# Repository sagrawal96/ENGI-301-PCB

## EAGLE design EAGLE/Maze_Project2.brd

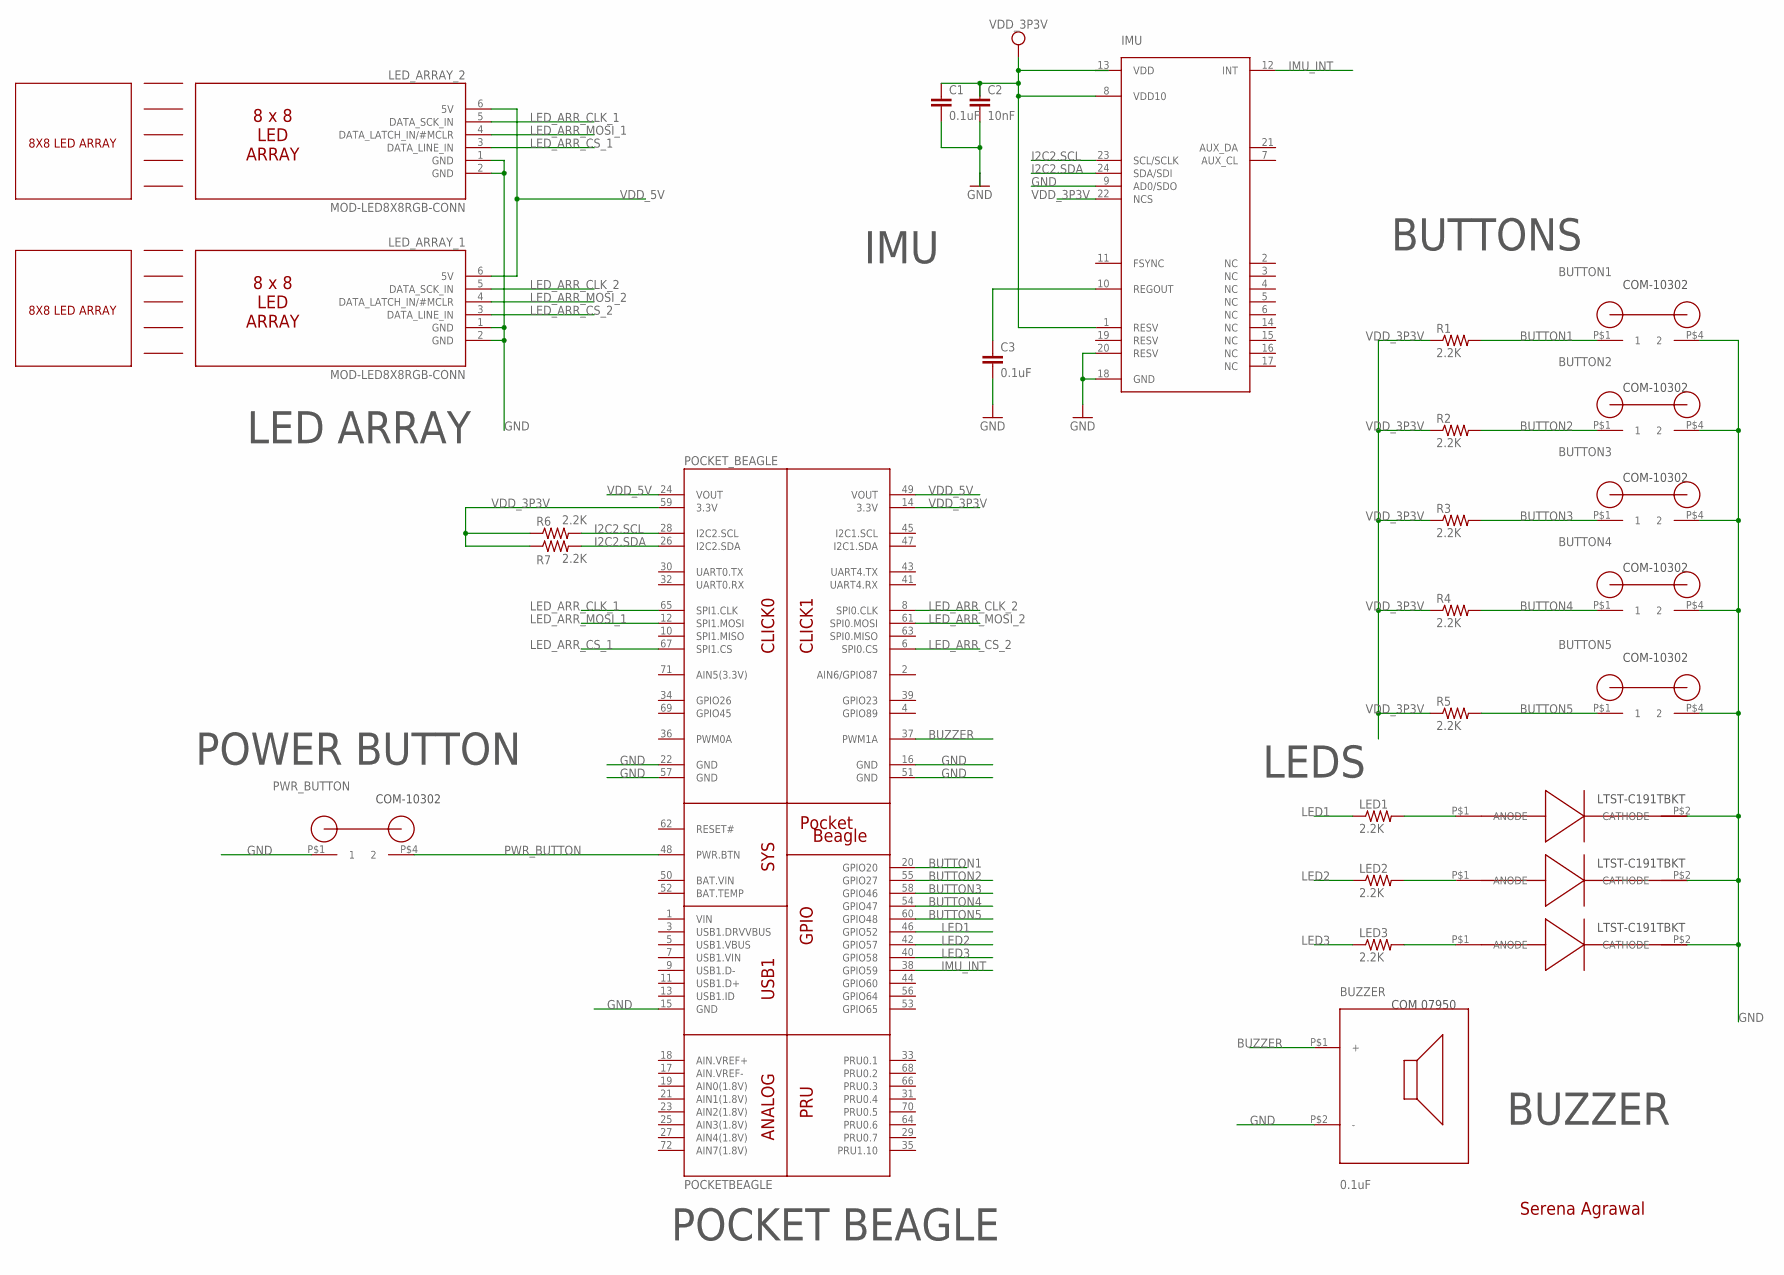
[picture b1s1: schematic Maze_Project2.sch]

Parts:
BUTTON1, BUTTON2, BUTTON3, BUTTON4, BUTTON5: BUTTON
BUZZER: 0.1uF; BUZZER
C1, C3: 0.1uF; C0402
C2: 10nF; C0402
IMU: MPU-9250; QFN-3MMX3MM
LED1, LED2, LED3: 2.2K; R0402
LED_ARRAY_1, LED_ARRAY_2: MOD-LED8X8RGB-CONN; FE06W
POCKET_BEAGLE: POCKETBEAGLE
PWR_BUTTON: BUTTON
R1, R2, R3, R4, R5, R6, R7: 2.2K; R0402
U$7, U$8, U$9: LED

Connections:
B: C3.2, IMU.18 (GND), IMU.20 (RESV)
BUTTON1: BUTTON1.P$1 (1), POCKET_BEAGLE.20 (GPIO20), R1.2
BUTTON2: BUTTON2.P$1 (1), POCKET_BEAGLE.55 (GPIO27), R2.2
BUTTON3: BUTTON3.P$1 (1), POCKET_BEAGLE.58 (GPIO46), R3.2
BUTTON4: BUTTON4.P$1 (1), POCKET_BEAGLE.54 (GPIO47), R4.2
BUTTON5: BUTTON5.P$1 (1), POCKET_BEAGLE.60 (GPIO48), R5.2
BUZZER: BUZZER.P$1 (+), POCKET_BEAGLE.37 (PWM1A)
GND: BUTTON1.P$4 (2), BUTTON2.P$4 (2), BUTTON3.P$4 (2), BUTTON4.P$4 (2), BUTTON5.P$4 (2), BUZZER.P$2 (-), IMU.9 (AD0/SDO), LED_ARRAY_1.1 (GND), LED_ARRAY_1.2 (GND), LED_ARRAY_2.1 (GND), LED_ARRAY_2.2 (GND), POCKET_BEAGLE.15 (GND), POCKET_BEAGLE.16 (GND), POCKET_BEAGLE.22 (GND), POCKET_BEAGLE.51 (GND), POCKET_BEAGLE.57 (GND), PWR_BUTTON.P$1 (1), U$7.P$2 (CATHODE), U$8.P$2 (CATHODE), U$9.P$2 (CATHODE)
I2C2.SCL: IMU.23 (SCL/SCLK), POCKET_BEAGLE.28 (I2C2.SCL), R6.2
I2C2.SDA: IMU.24 (SDA/SDI), POCKET_BEAGLE.26 (I2C2.SDA), R7.2
IMU_INT: IMU.12 (INT), POCKET_BEAGLE.38 (GPIO59)
LED1: LED1.1, POCKET_BEAGLE.46 (GPIO52)
LED2: LED2.1, POCKET_BEAGLE.42 (GPIO57)
LED3: LED3.1, POCKET_BEAGLE.40 (GPIO58)
LED_ARR_CLK_1: LED_ARRAY_2.5 (DATA_SCK_IN), POCKET_BEAGLE.65 (SPI1.CLK)
LED_ARR_CLK_2: LED_ARRAY_1.5 (DATA_SCK_IN), POCKET_BEAGLE.8 (SPI0.CLK)
LED_ARR_CS_1: LED_ARRAY_2.3 (DATA_LINE_IN), POCKET_BEAGLE.67 (SPI1.CS)
LED_ARR_CS_2: LED_ARRAY_1.3 (DATA_LINE_IN), POCKET_BEAGLE.6 (SPI0.CS)
LED_ARR_MOSI_1: LED_ARRAY_2.4 (DATA_LATCH_IN/#MCLR), POCKET_BEAGLE.12 (SPI1.MOSI)
LED_ARR_MOSI_2: LED_ARRAY_1.4 (DATA_LATCH_IN/#MCLR), POCKET_BEAGLE.61 (SPI0.MOSI)
unnamed: C1.2, C2.2
unnamed: C3.1, IMU.10 (REGOUT)
unnamed: LED1.2, U$7.P$1 (ANODE)
unnamed: LED2.2, U$8.P$1 (ANODE)
unnamed: LED3.2, U$9.P$1 (ANODE)
PWR_BUTTON: POCKET_BEAGLE.48 (PWR.BTN), PWR_BUTTON.P$4 (2)
SYS_VDD1_3P3V: C1.1, C2.1, IMU.1 (RESV), IMU.8 (VDD10), IMU.13 (VDD)
VDD_3P3V: IMU.22 (NCS), POCKET_BEAGLE.14 (3.3V), POCKET_BEAGLE.59 (3.3V), R1.1, R2.1, R3.1, R4.1, R5.1, R6.1, R7.1
VDD_5V: LED_ARRAY_1.6 (5V), LED_ARRAY_2.6 (5V), POCKET_BEAGLE.24 (VOUT), POCKET_BEAGLE.49 (VOUT)

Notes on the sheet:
Serena Agrawal
8X8 LED ARRAY
COM 07950
COM-10302
LTST-C191TBKT
LEDS
BUTTONS
BUZZER
IMU
LED ARRAY
POCKET BEAGLE
POWER BUTTON

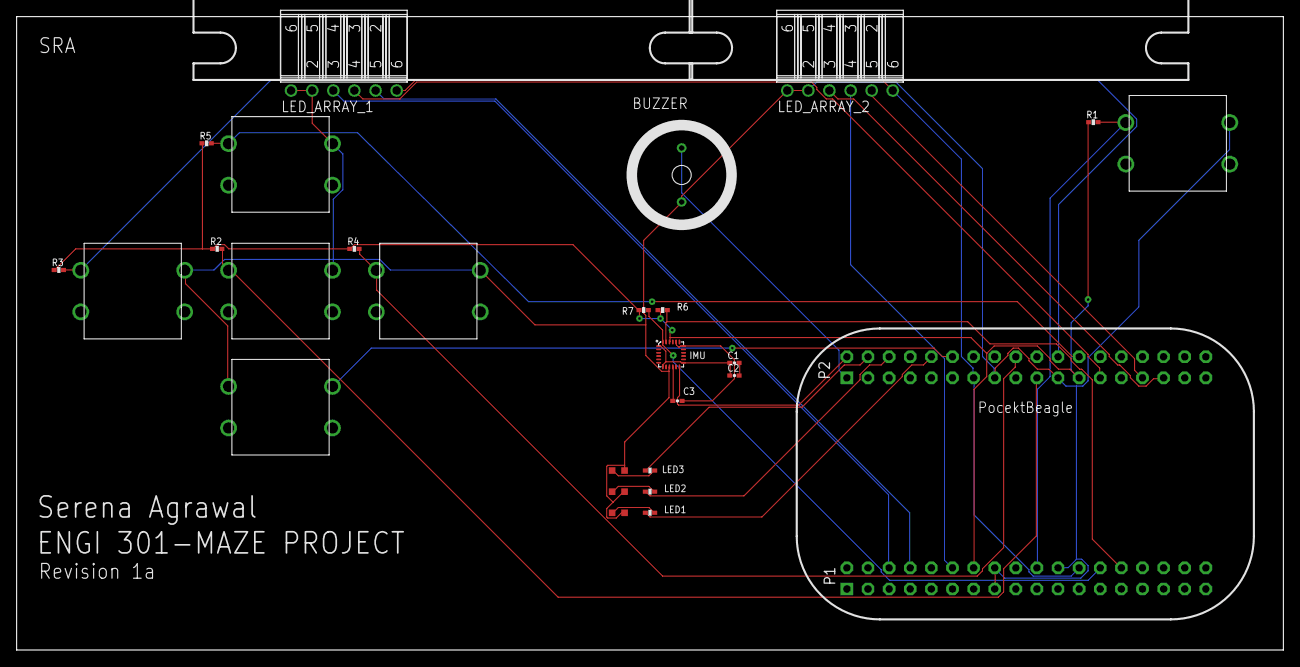
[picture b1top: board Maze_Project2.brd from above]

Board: 4 copper layers, 152.4 x 76.2 mm, 31 parts (0 on the bottom side), 29 nets.

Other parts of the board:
U$1, U$2, U$3, U$4: MOD-LED8X8RGB

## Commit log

2018-04-20 Final PCB Project 2a
    ENGI 301 Project 2a
2018-04-20 ACTUAL Final Project 2a
    The previous one had all the backups, this one is just the final .sch and .brd files
